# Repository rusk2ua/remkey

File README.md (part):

# remkey — remote paddle CW for the IC-7610 (or any rig with a KEY jack)

> **Status:** the software is complete and tested in CI (simulation, end-to-end network tests, and firmware builds for every Nano image), and it now runs end to end on the author's station (Oct 2026): a Mac paddle over Tailscale keys the IC-7610 and its tower-mounted 10 GHz transverter, with graceful PTT release and every safety stop checked. The tower telemetry (remtlm) has not yet run on real hardware. Sections 7 and 9 have the first-power-up checklists. Reports from real stations are very welcome.

Send CW with your own paddle from anywhere, with an instant local sidetone, and have the shack re-key it with perfect timing. Remote PTT (the TRANSMIT button) included.

remkey is built for a station where:

- A Windows PC in the shack already runs N1MM+, rig control and rotator control, and you reach it with AnyDesk.
- The 7610 drives a tower-mounted 10 GHz transverter through its SEND line, so PTT is manual and keying is CW.
- You travel with a Mac and want to use a real paddle.

It is two Arduino Nanos running the same sketch, plus a small Python bridge. Optional extra Nanos (**remtlm**, section 9) bring tower-top PA power, temperatures, reference lock and Kuhne transverter status, plus the tower supply's voltage and current from a box at the tower base, into the radio room over a LoRa link.

**Quick start:** wire and flash the Nanos (sections 1–3), run the station service on the shack PC (section 4), pick a network path (section 5), and run the client on your Mac (section 6). Do the bench test (section 7) before connecting anything to the tower. For a step-by-step checklist from ordering parts to a hardened station, see [docs/build-plan.md](docs/build-plan.md).

## How remkey works

**In one paragraph:** remkey lets you send CW with your own paddle, from anywhere with an internet connection, through the radio in your shack. A keyer at your end turns your paddle into characters, the characters cross the internet, and a second keyer in the shack sends them to the radio with perfect timing. You hear your own sidetone instantly, and the radio's real sidetone comes back in the receive audio a moment later.

**1. At the travel end, you hear yourself instantly.** The paddle and a PTT switch plug into an Arduino Nano that is an ordinary iambic keyer with its own sidetone, so there is no delay at all in what you hear. As you send, it decodes each character and passes it over USB to the remkey client on the Mac. The client also lets you type CW from the keyboard, has hotkeys for PTT, speed and a tune carrier, and shows tower readings.

**2. Only characters cross the network.** Sending raw key-down and key-up events over the internet doesn't work: network jitter stretches and chops the elements. remkey sends whole characters instead, along with PTT commands and a heartbeat every second, over an authenticated TCP connection (normally inside a Tailscale tunnel). Jitter can delay a character, but it can never distort one.

**3. The shack re-times them perfectly.** The station service on the shack PC checks the client's login and watches the heartbeat. It hands each character to a second Nano, which keys the IC-7610's KEY jack and SEND (PTT) line through optocouplers with exact timing. The SEND line in turn keys the 10 GHz transverter and PA on the tower. The radio runs about one character behind you, which is under a second at normal speeds.

**Feedback.** When the station has actually turned PTT on, the client's PTT LED lights. The receive audio, including the radio's own sidetone, comes back by AnyDesk, so you can confirm what really went out.

**Safety.** If the connection closes, the heartbeat stops for 3 s, or the shack PC or its USB link hangs (the station Nano has its own 3 s watchdog), PTT drops and any queued CW is thrown away at once. Characters sent while the link is down are dropped, not saved, so stale CW never goes out minutes later. N1MM+, rig control and rotator control keep running on the shack PC as before; remkey only adds the keying path.

The same picture as plain text:

```
  TRAVEL END (Mac)                                         SHACK (Windows PC)
 ┌───────────────────────┐                               ┌─────────────────────────────┐
 │ paddle ─┐             │                               │                             │
 │ PTT btn ┼─► CLIENT    │ USB  remkey.client   TCP/JSON │ remkey.station   USB        │
 │ speaker◄┘   Nano      ├────► (Python)  ─────────────────► (Python)  ──────► STATION │
 │  (local sidetone,     │      keyboard CW,  internet   │  auth, heartbeat,  Nano     │
 │   decodes paddle      │      hotkeys       (port-fwd  │  safety-off on     │        │
 │   to characters)      │                   or Tailscale│  link loss         │        │
 └───────────────────────┘                     tunnel)   │       opto ─► KEY jack      │
                                                         │       opto ─► PTT/SEND      │
                                                         │  N1MM+ / SO2R+ untouched    │
                                                         └─────────────────────────────┘
```

## Why it works this way

Sending raw key-down/key-up events across the internet doesn't work: network jitter stretches and chops your dits and dahs. remkey splits the job instead:

1. **At your end,** the client Nano is a normal iambic keyer with its own sidetone. You hear yourself with zero latency. It decodes each character you send and reports it over USB, for example `K:C`.
2. **Characters** cross the network, not element timing.
3. **At the shack,** the station Nano re-sends each character with exact timing on an optocoupler across the 7610's KEY line.

The radio transmits each character roughly one character-time after you send it. That's under a second at 15–20 WPM, which doesn't matter on 10 GHz. You still hear the radio's real sidetone in the remote audio stream (delayed), so you can confirm what actually went out.

Anything the decoder doesn't recognize, such as SK or a fumbled character, is passed through as a raw element pattern like `{...-.-}`. The station sends it element-for-element, so nothing is lost or "corrected."

**Long dash strings (antenna peaking).** Hold the dah paddle and the far end hears zeros: once a 6th dah follows five, the client sends those five as `0` and keeps going, so the station starts sending about one group (~1.3 s at 18 WPM) after you start, rather than after you stop. When you let go, the leftover dashes go out as an ordinary character (T, M, O).

## Contents

```
firmware/remkey/remkey.ino     Nano sketch (both roles)
firmware/remkey/config.h       role, pins, defaults
firmware/platformio.ini        optional PlatformIO/VS Code build
firmware/remtlm/               tower telemetry over LoRa (tower, psu + base roles), section 9
host/remkey/station.py         shack service (Windows)
host/remkey/client.py          travel client (macOS; Linux works too)
host/remkey/protocol.py        network protocol, CW text sanitizer
host/remkey/telemetry.py       remtlm packet parsing, calibration, link statistics
host/remkey/tlmview.py         bench viewer for calibrating the PA power sense
host/remkey/powerstats.py      tower supply statistics from the CSV log; suggested alert limits
host/remkey/e220.py            read or program an E220 LoRa module through a USB serial adapter
host/remkey/dashboard.py       telemetry web dashboard served by the station service (section 9)
host/remkey/web/dashboard.html the dashboard page (self-contained: no internet needed)
host/remkey/cloud.py           uploads telemetry snapshots to S3 for the cloud copy (section 9)
cloud/                         CloudFormation template + Mac deploy script for the cloud copy
host/*.example.toml            config templates
host/tests/                    pytest: protocol, end-to-end over localhost, telemetry
tests/firmware_sim/            g++ simulation of the sketch (timing, decoder, watchdog)
.github/workflows/ci.yml       CI: Python on Linux/Windows/macOS, simulation, firmware builds
docs/build-plan.md             phased build checklist, parts to tower installation
docs/serial-commands.md        sending CW by hand from the Serial Monitor
CHANGELOG.md                   per-component versions and changes
CONTRIBUTING.md, SECURITY.md   how to run the checks; security model and reporting
```

---

## 1. Hardware

Circuit boards for all three nodes (KiCad, with JLCPCB-ready Gerbers) are in [`hardware/`](hardware/README.md). A bench prototype of the shack and supply-box nodes on ElectroCookie boards is in [`docs/prototype/`](docs/prototype/README.md).

### Parts

| Qty | Part | Notes |
|---|---|---|
| 2 | Arduino Nano (ATmega328P) | Clones are fine. CH340 USB chips need no driver on current macOS or Windows. |
| 2 | PC817 (or 4N25/4N35) optocoupler | Station only: one for KEY, one for PTT |
| 2 | 470 Ω resistor | Opto LED current, about 8 mA with bare PC817s |
| 2 | 220 Ω resistor | Instead of the 470 Ω, with a ready-made 2-channel opto board (its indicator LED drops extra voltage; see Station Nano) |
| 1 | 3.5 mm stereo jack | Client paddle input |
| 1 | Momentary pushbutton/footswitch, or an SPST toggle switch | Client PTT (set `ptt_switch` in `client.toml`) |
| 1 | Piezo sounder or small speaker + 100 µF cap | Client sidetone; or feed a headphone amp |
| 1 | 220 Ω resistor | Sidetone series resistor |
| 1 | 10 kΩ pot (optional) | Client speed knob. Set `USE_SPEED_POT 1`. |
| — | Cables to the 7610 KEY jack and PTT line | Station |

### Client Nano (travel keyer)

| Nano pin | Connects to | Notes |
|---|---|---|
| D2 | Paddle jack **tip** (dit) | Internal pull-up; the paddle contact closes to GND |
| D3 | Paddle jack **ring** (dah) | Internal pull-up; the paddle contact closes to GND |
| GND | Paddle jack **sleeve**, and the GND side of everything below | Common ground |
| D4 | PTT switch, other side to GND | SPST toggle: `ptt_switch = "latching"`. Momentary button or footswitch: `ptt_switch = "momentary"` (in `client.toml`) |
| D9 | 220 Ω → piezo (+); piezo (−) to GND | Sidetone. Or 220 Ω → 100 µF → small amp/headphone input, with 10 kΩ to GND for level |
| D12 | 1 kΩ → LED anode; LED cathode to GND | Optional. Lights when the **station** confirms PTT is on |
| A0 | 10 kΩ pot wiper; pot ends to 5V and GND | Optional speed knob. Set `USE_SPEED_POT 1` in `config.h` |
| 5V | Top of the speed pot | Only needed with the pot |
| D13 | On-board LED (no wiring) | Flashes with every element you send |
| USB | Mac | Power and serial |

Swap paddles in `config.h` (`SWAP_PADDLES`) instead of rewiring.

**LEDs (both roles):** the on-board LED (D13) flashes with the CW being sent: paddle elements on the client, re-keyed text on the station. `LED_ACTIVE_LOW` in `config.h` sets its polarity. It's 1 by default, for clones whose LED lights on LOW; set it to 0 for a genuine Nano. PTT state goes to an optional external LED on D12 (D12 ── 1 kΩ ── LED ── GND).

### Station Nano (shack)

```
            ┌──────────── PC817 #1 ─────────────┐
D10 ─ 470Ω ─┤1 anode               collector  4 ├── KEY line (tip) ──► 7610 KEY
GND ────────┤2 cathode             emitter    3 ├── KEY ground (sleeve)
            └───────────────────────────────────┘
            ┌──────────── PC817 #2 ─────────────┐
D11 ─ 470Ω ─┤1 anode               collector  4 ├── PTT/SEND-in line ──► 7610
GND ────────┤2 cathode             emitter    3 ├── chassis ground
            └───────────────────────────────────┘
```

The block diagram above shows bare PC817 chips with 470 Ω drive. The schematic below uses a modified ready-made 2-channel PC817 board instead, driven through 220 Ω (details of the modification follow).

| Nano pin | Through | Board terminal | Board output | Goes to |
|---|---|---|---|---|
| D10 (KEY) | 220 Ω | IN1 | V1 | 7610 KEY jack tip, Y-cabled with the SO2R+ keying output |
| D11 (PTT) | 220 Ω | IN2 | V2 | SO2R Box rear RCA **PTT** jack, center pin |
| GND | — | G (input side) | G (output side) | KEY sleeve and RCA shell (radio-side ground; *not* tied to the Nano GND) |

The optocouplers keep the Nano and PC USB ground galvanically separate from the radio, which matters on a station with a tower.

**Ready-made 2-channel PC817 boards** (sold as "817 Module 2 Channel Isolation") need two changes before they'll work here. Each channel has a 3 kΩ chip resistor (marked `302`) on the input side **and another in series with the output**:

- **Input 302:** in series with your own resistor it starves the LED (about 0.4 mA). Remove it and bridge the pads, then drive the LED from the Nano through 220 Ω: about 3 V across the board's input, LED clearly lit.
- **Output 302:** it forms a divider with the radio-side pull-up, so the "closed" output only gets down to about 1.6 V into a footswitch input with a pull-up of a few kΩ. KEY may still work while PTT doesn't. Remove it and bridge the pads; the closed output then reads about 0.1–0.2 V.
- The yellow jumper on each channel ties the output's emitter side to the board ground. Leave it off to keep the radio side fully isolated from the Nano.

With the 302s gone nothing on the output limits current, which is fine for key and PTT inputs (a few mA through the radio's own pull-up). Don't use the outputs to switch anything powered.

**KEY connection.** Both the SO2R+ and the remkey optocoupler are open-collector closures to ground, so they can safely share one line. Either:

- Y-cable the opto output in parallel with the SO2R+ keying output on the rear KEY jack (simplest; N1MM+ keeps working), or
- use the 7610's other key jack, configured for a straight key / external keyer.

Collector goes to the key line (tip), emitter to ground (sleeve). If keying does nothing, reverse it.

**PTT connection.** The opto has to put the *radio* into transmit, just like your TRANSMIT button. Your DC injector stays on the radio's SEND output and keeps working unchanged. Use an input that forces TX:

- **ACC socket SEND line:** on many Icom rigs this pin is bidirectional (it goes low on TX, and grounding it forces TX). Check the IC-7610 full manual's ACC pinout before wiring.
- **Front MIC connector PTT pin:** always a TX input. Check the manual for the pin number.

Do **not** wire the opto to the SEND output that drives your DC injector. That would key the transverter without the radio being in transmit.

**With a YCCC SO2R Box (plus):** the simplest PTT input is the box's rear RCA **PTT** footswitch jack. It keys the transmit-focus radio's PTT through the box's radio cable, so your SEND-driven sequencing works unchanged. (The DB25 is the box's auxiliary connector and has no PTT or key pins.) This is what the author uses, with the KEY opto in parallel with the box's keying output; N1MM+ and a local paddle through the box keep working.

---

## 2. Radio settings (IC-7610)

- **Break-in: OFF while operating remotely.** Then nothing goes up the IF cable unless PTT is on, which matches how you already operate (TRANSMIT first, then key). It also means stray keying with PTT off produces sidetone only.
- The jack the opto keys must be set for a **straight key / external keyer**, not paddles. The station Nano is the keyer.
- Keep the 7610's USB audio codec streaming to the shack PC so you can hear receive audio (and the radio's sidetone) through AnyDesk. See section 6.

---

## 3. Firmware

Build with the Arduino IDE (board **Arduino Nano**; processor "ATmega328P", or "Old Bootloader" for most clones) or with PlatformIO in VS Code.

**Arduino IDE.** Open `firmware/remkey/remkey.ino`. In `config.h`, set

```c
#define REMKEY_ROLE ROLE_CLIENT     // for the travel Nano
#define REMKEY_ROLE ROLE_STATION    // for the shack Nano
```

and upload each.

**PlatformIO:**

```
cd firmware
pio run -e client  -t upload --upload-port /dev/cu.usbserial-110
pio run -e station -t upload --upload-port COM7
```

**Check it.** Open a serial monitor at 115200 baud with line ending set to newline. You should see `V:remkey 0.4.1 client` (or `station`; the number is the firmware version). Type `?` to get a status line. On the client, send a few characters with the paddle and you'll see `K:` lines. On the station, `T:CQ` keys the opto and `P:1` / `P:0` drive PTT.

Station watchdog: with PTT on or text queued, if the Nano hears nothing from the PC for 3 s it drops PTT, flushes text and prints `!:WDOG`. The service sends a heartbeat every second, so this only fires if the service or PC hangs.

The serial command set is documented at the top of `remkey.ino`. For keying a Nano by hand from the Serial Monitor, see [docs/serial-commands.md](docs/serial-commands.md).

---

## 4. Shack PC: station service (Windows)

1. Install Python 3.11+ from python.org (tick "Add to PATH").
2. Install remkey:
   ```
   cd remkey\host
   .\Install-remkey.bat
   ```
   It installs into the same Python that `Start-remkey.bat` (step 6) runs: `host\.venv` if you've made one, otherwise `py`. Use it for every later update too (`git pull`, then `.\Install-remkey.bat`). Installing with a bare `py -m pip ...` while a `.venv` exists puts packages where the station never looks: the code itself still updates, because the install is editable, but new dependencies (like boto3 for the cloud copy) go missing.
3. Configure:
   ```
   py -m remkey.genkey                  (copy the output)
   copy station.example.toml station.toml
   ```
   Edit `station.toml`: paste the secret and set `keyer_port` to the station Nano's COM port (Device Manager → Ports; *not* the SO2R+ or 7610 port).
4. Test without hardware:
   ```
   py -m remkey.station --config station.toml --dry-run
   ```
5. Run for real:
   ```
   py -m remkey.station --config station.toml
   ```
6. To start it automatically, use `host\Start-remkey.bat`. It runs the service from the `host` folder (using `host\.venv` if you made one, otherwise `py`), titles the window "remkey station", and if the service ever stops it leaves the window open with the exit code. Create a Task Scheduler task:
   - **Name:** remkey station. **Trigger:** At log on (your user).
   - **Action:** Start a program. **Program/script:** the full path to `Start-remkey.bat`. **Start in:** the `host` folder.
   - **Turn off console QuickEdit** for your user, once, in a Command Prompt:
     ```
     reg add HKCU\Console /v QuickEdit /t REG_DWORD /d 0 /f
     ```
     With QuickEdit on, a click in the window while it's opening at logon can put it into "Select" mode, which freezes the service until a key is pressed. remkey also turns QuickEdit off itself, but only once Python has started. The registry setting closes that gap.

   To check it, reboot, and before touching the window, connect a client and key PTT. Log lines should appear without pressing anything.

The service logs to the console and `remkey-station.log`. It accepts one client at a time.

---

## 5. Getting from the road to the shack

The client makes one outbound TCP connection. Pick one option; all work with the same software.

### Recommended: Tailscale

Encrypted, nothing exposed on the router, and it works with a VPN such as NordVPN running on the shack PC. Set `listen_host = "127.0.0.1"`, publish the port to your tailnet with `tailscale serve --bg --tcp 7373 tcp://127.0.0.1:7373`, and point `station_host` at the shack PC's Tailscale address. Full setup, including NordVPN coexistence: [docs/remote-access-tailscale-nordvpn.md](docs/remote-access-tailscale-nordvpn.md).

### Option A: router port-forward (free)

- On the Spectrum router, forward **TCP 7373** to the shack PC's LAN IP. Give the PC a DHCP reservation first.
- Windows Defender Firewall: allow inbound TCP 7373 for `python.exe`. Windows usually prompts on first run.
- In `station.toml`, set `listen_host = "0.0.0.0"`.
- In `client.toml`, set `station_host` to your public IP. Check it from the shack PC over AnyDesk if it ever changes.

**Security model:** a challenge-response HMAC with your secret (a fresh nonce every connection, so it can't be replayed), one client at a time, and a CW text whitelist. Traffic isn't encrypted. CW text isn't secret, and the risky operation is PTT, which needs the secret. Use a long generated secret.

### Option B: AnyDesk TCP tunnel (nothing exposed on the router)

This requires an AnyDesk plan that includes TCP tunneling.

1. In `station.toml`, set `listen_host = "127.0.0.1"`.
2. In AnyDesk on the Mac, open the shack PC's entry and choose **TCP tunnel → forward**: local port 7373 → `127.0.0.1:7373` on the remote side.
3. In `client.toml`, set `station_host = "127.0.0.1"`. The tunnel exists only while the AnyDesk session is open.

---

## 6. Mac: client

1. Install Python 3.11+ (`brew install python`), then:
   ```
   cd remkey/host
   python3 -m pip install -e .
   cp client.example.toml client.toml
   ```
   Paste the same secret, and set `station_host`, `station_port` and `keyer_port` (`ls /dev/cu.usbserial-* /dev/cu.usbmodem*`).
2. Run it in a terminal window:
   ```
   python3 -m remkey.client --config client.toml
   ```
   Without the travel Nano you still get keyboard CW: add `--dry-run`.

### Hotkeys

| Key | Action |
|---|---|
| PTT button on the keyer, or **Ctrl-T** | Toggle station PTT (the D12 PTT LED lights when the station confirms). Turning PTT off is a graceful release (see below). Pressing it again during the release keeps PTT on. |
| PTT toggle switch (`ptt_switch = "latching"`) | ON turns station PTT on, OFF is the graceful release. After a safety stop with the switch still ON, turn it off and on again to transmit; a switch left ON when the client starts doesn't key. Ctrl-T still toggles. |
| **Esc** | Abort queued text and any tune carrier. During a release, also drops PTT immediately. |
| **Ctrl-U** | Tune carrier (`tune_ms`, capped by the station). Needs PTT on. |
| **Ctrl-F / Ctrl-S** | Speed +1 / −1 WPM, both ends |
| **Ctrl-G** | Status: link, PTT, WPM, round-trip time (plus tower telemetry if fitted) |
| **Ctrl-P** | Tower: PA power, transverter power, temperatures, 10 MHz reference lock |
| **Ctrl-K** | Tower: Kuhne MKU 10 G5 status (`s`) and firmware version (`v`) |
| **Ctrl-V** | Tower: supply voltage and current, measured cable resistance and drop |
| **Ctrl-Q / Ctrl-C** | Quit. With PTT on, it first lets the station finish sending and release PTT (up to 15 s). Press again to quit at once. |
| Typing | Sent as CW. Enter sends a space. `<SK>`, `<AR>`, `<BT>`, `<KN>` send prosigns. |

### A typical 10 GHz QSO

1. In AnyDesk, set the frequency and point the dish with GH Everyware as usual.
2. Press the PTT button. Wait for the PTT LED (station confirmed), then wait for the tower sequencer as you would locally.
3. Send with the paddle. Your local sidetone paces you; the remote audio lets you confirm.
4. Press the PTT button again when you've finished sending. You don't need to wait for the station to catch up: it keys out everything still queued, holds PTT for 2 s more, then drops it. The client shows `STATION PTT releasing` until then, and the PTT LED stays lit.

### PTT release

The station runs about one character behind you, so pressing PTT off right after your last character would otherwise cut it short. Instead, PTT-off is a graceful release:

- The station Nano keys out everything already queued, then holds PTT for `ptt_hang_ms` (2000 ms by default, set in `station.toml`).
- Any CW that arrives during the hold (a character still in flight from the paddle, or you deciding to keep sending) is keyed and restarts the hold. **PTT never drops while CW is still being sent.** There is no upper limit; the hold ends only when nothing has been sent for the hang time.
- Pressing PTT again during the hold keeps PTT on. **Esc** during the hold drops PTT at once.
- The client Nano reports a character you've just finished before the PTT button press, so it reaches the station ahead of the release.
- The safety stops below are never delayed by the hold.

### Audio

The receive audio path is independent of remkey. AnyDesk's own audio transmission carries it one way (radio → shack PC → Mac); this setup is verified on the IC-7610, on Windows 10 and on Windows 11 with AnyDesk 9. Open the classic Sound panel with **Win+R → `mmsys.cpl`** (Windows 11: Settings → System → Sound → More sound settings).

1. **Sound → Recording:** the 7610's input (e.g. *Microphone – 3- USB Audio CODEC*, or the name you gave it) → Properties → **Listen** → tick **Listen to this device**, playback through the default output chosen by name. **Leave it ticked permanently:** it isn't a test feature, it's the only thing that puts the radio's audio where AnyDesk can capture it. It's stored per device, so it doesn't survive a move to a new PC or a new USB port.
2. **Sound → Playback:** the default (green check) is the PC's normal output, e.g. an HDMI monitor. It doesn't need speakers; it just has to show *Ready* / *Default Device*. **Never** make *Speakers – USB Audio CODEC* the default: that's the radio's transmit input.
3. **AnyDesk on the shack PC → Settings → Audio:** **Audio Transmission = "Audio output of this device"**, not the radio's codec. (Pointing it at the codec sends the silent transmit side, so the Mac hears nothing.)
4. **AnyDesk → Settings → Permissions** (AnyDesk 9: **Settings → Access**): "Hear my device's sound" ticked in both the **Unattended Access** and **Default** profiles.
5. **Restart AnyDesk on the shack PC and reconnect** after any audio change; a running session doesn't pick it up.

Quick check: play a YouTube video on the shack PC. If you hear it on the Mac but not the radio, the Listen box (step 1) is unticked or points at a different output. Don't go by the Playback tab's level meter: on AMD HDMI/DP audio (GMKtec G10) it stays flat even when audio is flowing; the Intel NUC's meter moved. Use the Recording tab meter to see the radio reaching the PC, and your ears on the Mac for the rest. If an HDMI monitor sleeps, Windows may drop its audio device, so set the display to never turn off. Before relying on it, confirm the radio's CW sidetone is present in the stream: key the rig locally with BK-IN off and listen.

### Safety layers

Every one of these drops PTT and flushes queued text **immediately**, with no release hold:

| Event | Where |
|---|---|
| TCP connection closes or errors | station service |
| No heartbeat from the client for 3 s (dead hotel Wi-Fi, laptop sleeps) | station service |
| Station service or PC hangs, USB unplugged | station Nano watchdog (3 s) |
| Tune carrier | capped by the service (`max_tune_ms`) and the firmware (30 s hard cap) |

Quitting the client is not on this list: it requests a normal release and waits for it (up to 15 s, or press Ctrl-Q again).

Paddle characters sent while the link is down are **dropped**, not buffered, so stale CW never goes out minutes later.

---

## 7. Bench test before connecting to the tower

1. Station Nano on the PC, opto outputs to a multimeter (continuity) or LEDs, not the radio yet.
2. Run the service, connect the client on the same LAN (`station_host` = the PC's LAN IP), and check:
   - PTT button → PTT opto closes, D12 PTT LED on at both ends.
   - Paddle → KEY opto follows about one character behind; local sidetone is immediate.
   - Kill the client's Wi-Fi with PTT on → PTT opens within 3 s.
   - Stop the service with PTT on → the Nano opens PTT within 3 s (`!:WDOG`).
   - Unplug the station Nano's USB with PTT on → PTT opens at once (the Nano loses power). Plug it back in: the service reconnects and re-arms it by itself.
   - Unplug the client Nano's USB with PTT on → the client releases PTT gracefully (queued CW still goes out, then the hang). Plug it back in: the paddle works again without restarting the client.
3. Connect to the 7610 into a dummy load at the IF with the transverter disabled. Check KEY polarity and PTT.
4. Test from your phone's hotspot over the port-forward or tunnel.

---

## 8. Development

```
cd host && python3 -m pip install -e ".[test]" ruff && ruff check . && python3 -m pytest -q
tests/firmware_sim/run.sh       # needs g++; runs the sketch against a mock Arduino
```

GitHub Actions runs all of this on every push and pull request, plus an `arduino-cli` build of every firmware image (remkey client and station; remtlm tower, tower with its own INA226, base and psu). The resulting `.hex` files are attached to each CI run as artifacts. See CONTRIBUTING.md.

The firmware simulation checks:

- PARIS at 20 WPM takes exactly 46 units with 22 units of key-down.
- Raw patterns and word spacing.
- Iambic A/B squeeze behavior.
- Paddle decode of `CQ TEST K2UA`, and unknown patterns.
- Tune timing and the 30 s cap.
- The watchdog, with and without heartbeats.
- PTT button debounce.
- That the client paddle never drives the KEY output.
- remtlm (mocked E220, OneWire and INA226): the psu node slots its `$RS` ~60 ms after each tower `$RT`, falls back to its own 2 s timer when the tower is silent, ignores corrupt packets, reports a missing INA226 and a reversed shunt; the tower sends `$RP` only with `PWR_ENABLE 1`; the base forwards `$RS` and counts bad packets.

Every firmware image builds with no warnings in the project's own files (`arduino-cli`, board Arduino Nano, `--warnings all`):

| Image | Flash | Static RAM |
|---|---|---|
| remkey client / station | 7.9 KB of 30 KB | 541 B of 2 KB |
| remtlm tower with its own INA226 (`PWR_ENABLE 1`; 0.3.0 figures) | 18.8 KB | 1056 B |
| remtlm psu | 17.5 KB | 832 B |
| remtlm base | 7.8 KB | 458 B |

Library versions used in CI: EByte LoRa E220 library 1.0.8, OneWire 2.3.8, DallasTemperature 4.0.6.

## 9. Tower telemetry (remtlm)

Three more Nanos bring tower readings into the radio room over one LoRa channel. Two of them transmit, from two boxes on the tower, and one receives in the shack.

### How remtlm works

**In one paragraph:** remtlm tells you what's happening on the tower while you operate. Two small boxes on the tower measure the things the radio can't see, such as PA output, reference lock, temperatures, supply voltage and dish elevation, and send them by LoRa radio to a receiver in the shack. The station service that already runs remkey turns the readings into hotkey readouts, alerts, a live web dashboard and an optional cloud copy you can check from anywhere.

**1. The tower-top box reports what the rig can't see.** A Nano in the box on the back of the dish watches the PA's power-sense output, the transverter's own power monitor, its 10 MHz reference lock and its key line to the sequencer, sampling every 5 ms so that even a single CW dit is caught. It also reads two temperature probes, the transverter's serial status (read-only), the dish elevation from an ADXL355 on the dish frame, and the box's air temperature, humidity and pressure. It sends a short report every 2 seconds, every half second while the PA is transmitting, and an elevation reading 5 times a second while the dish moves.

**2. The supply box reports on its own.** A second Nano, in the supply box at the tower base, measures the voltage and current going up the tower cable and the box temperature. It is separate so it can be built first and keeps reporting even if the top box is down. Both boxes share one radio channel: the supply box listens for each tower report and sends its own in the gap right after it, so the two never collide.

**3. One program shows it everywhere.** In the radio room, a third Nano with its own LoRa radio checks every packet and adds the signal strength, then passes it over USB to the station service. The service applies the calibrations, raises alerts (reference unlock, over-temperature, low or high supply, the transverter keyed but no PA output, a stuck key line, humidity or condensation in the box, a box gone silent), logs everything to a CSV file, and shows it on the Mac client's hotkeys, a live web dashboard and an optional read-only cloud page.

**Why radio, and why it's safe.** The LoRa link means there is no wire between the tower and the house, so it adds no lightning path. Telemetry uses its own USB port, separate from the remkey station Nano, so a telemetry fault can't affect keying. Nothing in remtlm can key the radio or change the transverter's settings: the tower only ever asks the transverter for its status.

### What each box measures

The **tower-top box** (TOWER image) is set up for a **Kuhne MKU 10 G5** transverter and an external PA:

- **PA power sense** (0–5 V), peak and average, sampled every 5 ms so CW dits aren't missed
- **MKU MON** output (CON1 pin 9), the transverter's own power monitor
- **10 MHz reference lock** from the MKU's LD output (CON1 pin 16); any unlock during a reporting interval is reported
- **The key line to the sequencer** (MKU CON1 pin 8, PTT out, active low; tower firmware 0.6.0+): whether it was keyed during each interval, and its voltage. Changes are reported right away. It tells you which side failed when the MKU transmits but the PA doesn't, and it catches a key line stuck low
- **Two DS18B20 probes**: PA heatsink and MKU case
- **The MKU's serial status**: the `v` (firmware) reply once after boot, then the `s` (status) reply every minute, relayed verbatim
- **Dish elevation** (tower firmware 0.7.0+): one ADXL355 on the frame that carries both dishes (10 and 24 GHz, one actuator). The dashboard shows it on an analog-style dial, updated 5 times a second while the dish moves
- **Box air** (0.7.0+): a BME280 in the box for temperature, humidity, pressure and dew point, with a condensation alert

The **supply box at the tower base** (PSU image) is separate, so it can go in before the top box and keeps reporting if the top box is down:

- **Supply voltage and current** going up the tower, from an INA226 and a shunt at the supply output: min, average and peak for every interval
- **One DS18B20** for the box temperature
- Its own sequence number and uptime, so the station tracks its link loss and resets separately

The top box can optionally get its own INA226 as well (`PWR_ENABLE 1`). With both, the station shows the **measured cable drop**, works out the **cable's actual resistance**, and checks the voltage the MKU actually sees (see "Supply voltage, current and cable drop" below).

```
 TOWER TOP                                                  RADIO ROOM
┌──────────────────────────────────────────┐            ┌──────────────────────────────┐
│ PA sense ─────────► A0 ┐                  │  927.125   │ E220 ─► BASE Nano ─USB─► PC   │
│ MKU pin 9 MON ────► A1 │                  │    MHz     │  validates packets   station  │
│ MKU pin 16 LD ────► A2 ├─ TOWER ─► E220 ~~~~~~~~~~~~~~►│  from both boxes     service  │
│ MKU pin 8 PTT out ► A3 │                  │            │                              │
│ DS18B20 ×2 ───────► D5 │   Nano     $RT  │    LoRa    │  ─► client: Ctrl-P, Ctrl-K,   │
│ MKU pins 11/12 ◄──► D11/D12 (via shifter)│     ▲      │     Ctrl-V, alerts, TX summary│
│ ADXL355, BME280 (+opt. INA226) ─► A4/A5  │     ║      │                              │
└───────────────▲──────────────────────────┘     ║      └──────────────────────────────┘
                ║ tower cable (+/−)              ║
 TOWER BASE     ║                                ║
┌───────────────╨──────────────────────────┐     ║
│ 14 V supply ═► shunt ═► tower cable       │     ║
│ INA226 on the shunt ─► A4/A5 ┐            │     ║
│ DS18B20 (box temp) ──► D5    ├─ PSU ─► E220 ~~~╝  $RS, just after each $RT it hears
│                              │  Nano      │
└──────────────────────────────────────────┘
```

There is no conductor between the tower and the house, so the link adds no lightning path. Everything ends up in the same station service and Mac client as remkey.

**The transverter link is read-only.** The tower only ever sends `s` and `v`, which read status, never the configuration commands (`IR`/`IT`/`RR`/`RT`/`D1`–`D4`). A garbled byte can't retune the IF or change the sequencer.

### Which Nano is which

With remtlm, the station has up to five Nanos. Each is a separate board on its own USB port or in its own box; the remtlm base does **not** replace the remkey station Nano.

| Nano | Where | Firmware | Connects to |
|---|---|---|---|
| remkey station | Shack PC (USB) | remkey, station role | `keyer_port` in `station.toml`, and the 7610 keying lines |
| remtlm base | Shack PC (USB) | remtlm 0.5.0, base | `tlm_port` in `station.toml`, plus its own E220 |
| remtlm psu | Supply box at the tower base | remtlm 0.4.0, psu | Its own E220, INA226, DS18B20 |
| remtlm tower | Tower-top box | remtlm, tower | Its own E220, PA and MKU sense lines, probes |
| remkey client | Travel end (Mac, USB) | remkey, client role | Paddle and PTT switch; the Mac client by USB |

The station service opens both shack ports. The keying path and the telemetry path share no hardware, so a telemetry fault can't affect keying: unplugging the remtlm base only raises a "lost" alert.

### Frequency and legality

- The link runs on **927.125 MHz** (E220-900T22D channel 77, set by `LORA_CHANNEL` in `firmware/remtlm/config.h`). That's the top of the US 902–928 MHz band and about 24 MHz clear of 902–903 weak-signal work.
- Treat the link as part of your **amateur station (Part 97)**. 927 MHz is in the 33 cm band, the packets are plain ASCII with no encryption, every packet carries your callsign, and §97.221(b) allows automatic control of data emissions on 6 m and shorter. It is *not* a Part 15 device in this configuration: a single-channel module at 17 dBm doesn't fit the unlicensed rules.
- Airtime: roughly 60–70 ms per packet at the 9.6 kbps air rate. The top box sends a `$RT` every 2 s while idle and every 0.5 s while the PA shows output (plus a `$RP` before each one if it has its own INA226). With the 0.7.0 sensors it adds a `$RA` (elevation, ~50 ms) before each `$RT`, a `$RB` (box air) every 10 s and a `$RC` (the BME280's calibration constants) every 5 minutes, all just ahead of a `$RT`.
- **Live elevation.** While the dish moves, the tower sends a `$RA` every 200 ms, until it has been still for 3 s; that uses about a quarter of the channel while it lasts, and nothing when the dish is parked. Live packets skip the 450 ms after each `$RT`, which is the supply box's slot, so the supply box keeps reporting while the dish moves. No MKU status poll starts while the dish moves.
- **Two transmitters, one channel.** The base E220 can only listen on one channel, so both boxes use channel 77. To keep them from colliding, the supply box listens too: it sends its `$RS` about 60 ms after the end of each tower `$RT` it hears, in the gap before the tower's next packet, which is at least 0.5 s away. If it hears no tower packet for 3.5 s (top box down, or not built yet), it sends every 2 s on its own timer. It never sends more often than every 0.4 s.
- Transmit power defaults to 17 dBm, which is plenty for 200 ft through block. Raise it with `LORA_TX_POWER` if the link is marginal.

### Parts

| Qty | Part | Notes |
|---|---|---|
| 3 | Ebyte E220-900T22D | All must be the **900** version |
| 3 | 915 MHz antenna (SMA) | A whip is fine; a small yagi at the house end if needed |
| 3 | Arduino Nano | Tower top, supply box, radio room |
| 9+9 | 1 kΩ and 2 kΩ resistors | 5 V → 3.3 V dividers on E220 M0, M1 and RXD, at each Nano |
| 3 | 100 µF electrolytic | Across the E220 VCC/GND pins (TX current peaks) |
| 2 | Mini buck module, fixed 5 V output (5–28 V in) + 0.5 A-hold polyfuse (e.g. RXEF050) | Tower top and supply box: supply → 5 V. Fixed output, nothing to set |
| 1 | AMS1117-3.3 module (or any 3.3 V LDO) | Tower: low-voltage side of the level shifter |
| 1 | 4-channel BSS138 level-shifter module | Tower: Nano ↔ MKU serial (3.3 V) |
| 2 | DS18B20 waterproof probes + one 4.7 kΩ resistor | Tower: both on one bus |
| 2 | 10 kΩ + 22 kΩ resistors, 100 nF caps | Tower: input dividers for A0 and A1 |
| 1 | 100 kΩ resistor | Tower: pull-down on A2 (LD) |
| 1 | 100 kΩ + 47 kΩ + 22 kΩ resistors, 100 nF cap | Tower: key-line network on A3 (MKU CON1 pin 8) |
| — | 2.54 mm female header/jumper wires | Tower: to MKU CON1 |
| 1 | INA226 module (e.g. CJMCU-226) | Supply box: supply monitor. Any I2C address 0x40–0x4F works: the firmware searches for it (0.7.1+) |
| 1 | 20 A / 75 mV panel-meter shunt (3.75 mΩ) | Supply box: in the + feed to the tower cable (see below) |
| 1 | DS18B20 probe + 4.7 kΩ resistor | Supply box: box temperature |
| 1 | Weatherproof box with cable glands | Tower |
| (1+1) | INA226 module + shunt | Optional, tower top (`PWR_ENABLE 1`): measured cable drop |
| 1 | ADXL355 breakout, wired for I2C | Tower (0.7.0+): dish elevation, on its own stiff plate on the dish frame |
| 1 | BME280 breakout (a real BME280: a BMP280 has no humidity) | Tower (0.7.0+): box air |
| 2 | 4-wire leads | Tower: to J2/J3 on RK-302 Rev B, or to the sensor board on a Rev A |

### Wiring: E220 to Nano (same on all three Nanos)

The E220's logic is 3.3 V and not every pin is 5 V tolerant, so the three Nano outputs go through dividers.

```
E220 pin   Nano
M0   ◄──── 2k ──┬── 1k ──── D9        (each divider: Nano ─1k─┬─ E220 pin
M1   ◄──── 2k ──┼── 1k ──── D10                               └─2k─ GND)
RXD  ◄──── 2k ──┼── 1k ──── D8
            GND ┘
TXD  ─────────────────────► D7
AUX  ─────────────────────► D6
VCC  ── 5 V ── 100 µF ── GND
GND  ── GND
```

### Wiring: tower Nano to the MKU 10 G5 and PA

```
13.8 V ── 1 A fuse ── buck (5.0 V) ──► Nano 5V pin (not VIN), E220 VCC, DS18B20s, shifter HV
                     5.0 V ── AMS1117-3.3 ──► shifter LV

PA sense      ── 10k ──┬── A0       MKU CON1 pin 9 (MON) ── 10k ──┬── A1
                       ├─ 22k ─ GND                                ├─ 22k ─ GND
                       └─ 100nF ─ GND                              └─ 100nF ─ GND

MKU CON1 pin 16 (LD) ─────────┬── A2        LD is 3.3 V via 330 Ω when locked; the
                              └─ 100k ─ GND  pull-down holds A2 low otherwise

MKU CON1 pin 8 (PTT out) ──┬── to the sequencer, as before (the tower only listens)
                           ├── 100k ── 5V   an open line reads ~2 V, not "keyed"
                           └── 47k ──┬── A3
                                     ├── 22k ─ GND     keyed (low) reads ~0 V; safe to ~15 V
                                     └── 100nF ─ GND

MKU CON1 pin 11 (TXD) ── shifter LV1 ═ HV1 ── D11
MKU CON1 pin 12 (RXD) ── shifter LV2 ═ HV2 ── D12
MKU CON1 pin 15 (GND) ── GND                (common ground with the Nano)

DS18B20 #1 and #2: red 5V, black GND, both yellow ── D5; one 4.7k from D5 to 5V

Optional (PWR_ENABLE 1 in config.h), a second INA226 at the top-box entry:
INA226 module: VCC ── 5V, GND ── GND, SDA ── A4, SCL ── A5   (A0/A1 address pins to GND)

 from tower cable (+)        20 A / 75 mV shunt            to everything in the box
 +13.8 ══════════► [big bolt]══════════════════[big bolt] ══════► MKU, PA, relays, fuse, buck
                   (sense screw)            (sense screw)
                        │                         │
                       IN+                       IN- ── also VBUS on modules that
                                                        have a separate VBUS pin
```

The same wiring as schematics, in two parts: the signals (PA sense, MKU CON1, level shifter and probes), then the power feed with the optional top-box supply monitor. Without it, the 13.8 V feed goes straight to the fuse and the equipment.

**Notes:**

- **Why analog for LD:** a 5 V Nano needs about 3.0 V to read a digital high, and LD gives only 3.3 V through 330 Ω. That's too close, so A2 compares against 1.65 V instead.
- **LD tracks the external 10 MHz reference:** it's high only while the MKU is locked to an *external* 10 MHz reference. If you run without one, set `LOCK_MONITOR 0` so it doesn't alarm (or, from 0.7.1, add `-DLOCK_MONITOR=0` to the arduino-cli build flags).
- **Probes:**
  - Clamp one DS18B20 under a heatsink screw near the PA device and the other on the MKU housing, both with thermal compound.
  - The MKU is rated for +55 °C case and disables transmit above +65 °C. The default alert for probe 2 is 50 °C.
  - Probe order on the bus is fixed by each probe's serial number, not by wiring. Warm one in your hand while watching `tlmview` to see which is which. Then set `temp_names` in `station.toml`, or swap the probes.
- **ADC reference:** the buck's output is fixed at 5 V, but each module is a little off. Measure the actual rail with a DMM and enter it as `VREF_MV`. The ADC uses that rail as its reference.
- **Command terminator:** if the MKU doesn't answer `s`, it may want a line terminator. Set `XV_CMD_SUFFIX "\r"` in `config.h`.

### Wiring: supply box at the tower base (PSU Nano)

The same Nano and E220 block as the other two, plus the INA226 on a shunt in the supply's + output, and one DS18B20:

```
14 V supply (+) ══╦══► [bolt] 20 A / 75 mV shunt [bolt] ══════► tower cable (+)
                  ║         (sense)        (sense)
                  ║            │              │
                  ║           IN+            IN- (and VBUS, if the module has one)
                  ╚═ 1 A fuse ── buck (5.0 V) ──► Nano 5V pin (not VIN), E220 VCC, INA226 VCC, DS18B20

INA226 module: VCC ── 5V, GND ── GND, SDA ── A4, SCL ── A5   (A0/A1 address pins to GND)
DS18B20: red 5V, black GND, yellow ── D5; 4.7k from D5 to 5V
E220: same as "Wiring: E220 to Nano" above
14 V supply (−) ── tower cable (−) ── box ground (buck, Nano, E220, INA226)
```

- **Take the box's own 5 V from the supply side of the shunt.** Then the INA226 measures only what goes up the tower, not the box's own 30–120 mA.
- **The voltage reported is the supply's output** (load side of the shunt), not the voltage at the top. The cable drop is only measured once the top box has its own INA226; until then, Ctrl-V shows supply voltage and current only.
- **Antenna:** the supply box is closer to the house than the top box, so a whip on the box is plenty. Keep it a few feet from the tower cable.
- **Don't power the Nano from VIN at 14 V.** Its linear regulator would drop 9 V at up to ~120 mA during E220 transmit peaks, more than 1 W in a sealed box. Use a buck module or a 5 V USB supply.

**Supply monitor notes** (the supply box's INA226, and the optional one at the top):

- **Put the shunt ahead of everything it should measure.** In the supply box that is the feed to the tower cable. At the top it is the enclosure entry, ahead of everything including the tower Nano's own buck converter.
- **Heavy wires go on the big bolts; IN+ and IN- go on the small sense screws.** The sense screws give you a Kelvin connection: they measure the shunt element itself, not the resistance of the bolted joints. IN+ goes on the supply side, IN- on the load side.
- **The whole shunt sits at +13.8 V.** Mount it on its insulating base or on standoffs, clear of the metal enclosure, and cover the terminals.
- **Range:** with 3.75 mΩ the INA226 reads up to 21.8 A in 0.67 mA steps. At 4 A the shunt drops 15 mV and dissipates 60 mW; at 8 A, 30 mV and 0.24 W. Panel shunts run cool well below their rating.
- **`SHUNT_UOHM` is 3750 by default.** A different shunt needs only that value changed: millivolt rating ÷ amp rating, in µΩ (75 mV / 20 A = 3750).
- **CJMCU-226 modules have their own 0.1 Ω shunt (R100) on the board.** Remove it. Left in parallel with the panel shunt it makes readings 3.6% low (or set `SHUNT_UOHM 3614`).
- **The bus voltage is read on the load side of the shunt.** At the top that is the voltage your equipment actually sees; in the supply box, it's what goes into the cable. On modules with a separate VBUS pin, tie it to IN-.
- **Negative current means the shunt is wired backwards.** It is reported as-is, not hidden.
- **Trim to your meters:** compare against a DMM at the INA226 and a clamp meter, then set `v_scale` and `i_scale` in `station.toml`. No reflash needed. (One pair of trims covers both INA226s; with good shunts and modules they need little or no trim.)

### Wiring: base Nano (radio room)

Only the E220 block above (its schematic covers all three), plus USB to the shack PC. It receives both boxes; nothing else is needed for the second sender, except that it must run remtlm 0.4.0 or later, because older base firmware rejects `$RS` packets as bad. Put the module and its antenna where it has the best view of the tower, for example a window. A USB extension cable is fine.

### Optional: check each E220 with a USB serial adapter

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
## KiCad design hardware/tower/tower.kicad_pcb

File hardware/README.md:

# remtlm circuit boards

Three two-layer boards for the remtlm telemetry nodes, all through-hole, built by hand, with the modules in sockets:

| Part number | Board | Folder | Size | Goes in | Holds |
|---|---|---|---|---|---|
| RK-301 Rev A | Supply box (PSU) | `psu/` | 102 × 52 mm | Hammond 1590B at the tower base | Nano, INA226 module, mini buck, polyfuse, E220 dividers, one DS18B20 |
| RK-302 Rev B | Tower top | `tower/` | 102 × 52 mm | Hammond 1590B at the tower top | Nano, mini buck, AMS1117-3.3, BSS138 shifter, PA/MKU conditioning, key-line (MKU PTT out) sense, two DS18B20s, I2C headers for the dish elevation sensor (ADXL355) and box air sensor (BME280) |
| RK-303 Rev A | Shack (BASE) | `shack/` | 64 × 40 mm | No enclosure; USB from the shack PC | Nano, E220 dividers |

Part numbers, revisions and the rules for changing them are in [`REVISIONS.md`](REVISIONS.md). Each folder has the KiCad 7 board (`*.kicad_pcb`), a Gerber + drill zip for the fab (`fab/<pn>-rev<rev>-*-gerbers.zip`), a parts list (`*-bom.csv`), top and bottom renders (`img/`) and the DRC report (`*.drc.txt`).

## Checking the fit on paper

Each `fab/` folder has a `*-print-letter.pdf`: the pads, outlines, labels and board edge at full size on US Letter, with a 100 mm scale bar. Print it at 100% (Actual size, not Fit), then measure the bar. It must be exactly 100 mm. Push the modules' pins through the pad dots into a piece of foam or cardboard to check every footprint. (`*-print-1to1.pdf` is KiCad's own A4 plot of the same thing.)

## Ordering (JLCPCB)

Upload the zip from `fab/` as it is. Under "Remove Order Number", choose **Specify a location**: each board has `JLCJLCJLCJLC` printed under the Nano, where JLCPCB will put its number. The defaults are fine: 2 layers, 1.6 mm FR-4, 1 oz copper, HASL. The four buck-module holes are plated slots (1.0 × 2.2 mm). JLCPCB makes those without extra charge, and they show up as slots in the drill file.

## How the boards connect

The nets are the same as the schematics in `docs/img/`:

- `remtlm-psu-box-schematic.svg` (supply box)
- `remtlm-tower-signals-schematic.svg` and the logic-supply part of `remtlm-tower-power-schematic.svg` (tower top; there's no shunt or INA226 at the top)
- `remtlm-e220-schematic.svg` (all three)

The Nano pin numbers match `firmware/remtlm/config.h`. The KiCad files are boards only, not schematic files: each board is described in a short Python script in `gen/`, which places the parts and gives every pad its net. The Python script `gen/route.py` then checks every pad against that list after routing.

### Wires soldered into the board

| Wire | Hole | Pad | Used for |
|---|---|---|---|
| #16 | 1.8 mm | 3.6 mm | Supply in (+ and GND) |
| #18 | 1.4 mm | 2.8 mm | DS18B20 probes (GND, DQ, 5V) |
| #20 | 1.2 mm | 2.4 mm | Shunt Kelvin leads; MKU CON1 pins 11, 12, 16, 9, 15; PA sense and PA ground |

### E220 ribbon

The 1 × 7 header on each board runs M0, M1, RXD, TXD, AUX, VCC, GND, in the module's own pin order. The 5 V → 3.3 V dividers for M0, M1 and RXD are on the main board, so the ribbon carries 3.3 V-level signals. The board has 100 µF + 100 nF at the header. Put another 100 µF across VCC/GND at the E220 end of the ribbon, on the daughterboard.

## Build notes

- **Sockets and headers** (not in the BOMs):
  - Nano: two 1 × 15 female headers on every board.
  - Supply box: a 1 × 8 for the INA226 module.
  - Tower: two 1 × 6 for the shifter, a 1 × 3 for the AMS1117 module, and two 1 × 4 male headers (J2, J3) for the sensor leads.
  - Buck module: four header pins, one in each corner pad.
- **Buck module:** a fixed 5 V output module (5–28 V in), so there's nothing to set; measure its output once for `VREF_MV`. The board marks IN+, IN−, OUT+ and OUT− at the four slots. Check them against the labels printed on the module's underside before soldering. Viewed from above with the inductor on the right, the corners are IN− top-left, OUT− top-right, IN+ bottom-left and OUT+ bottom-right.
- **INA226 module (supply box):**
  - Remove its R100 shunt resistor; the external shunt does the work (or set `SHUNT_UOHM` as the README describes).
  - The board ties VBS to IN−, so bus voltage is measured on the tower side of the shunt.
  - SHUNT+ goes to the supply side of the shunt.
- **Polyfuse:** a radial PTC with 0.5 A hold / 1.0 A trip, rated for at least 30 V (e.g. Littelfuse RXEF050), on 5 mm lead spacing. It protects the board's own logic supply only; the main load current never passes through these boards.
- **Level shifter (tower):** the module sits rotated 180°, LV row toward the transverter wires. LV1 carries MKU TXD (CON1 pin 11) to D11, and LV2 carries MKU RXD (pin 12) from D12. On Rev B, channels 3 and 4 carry the sensors' I2C: LV3/HV3 is SDA (Nano A4), LV4/HV4 is SCL (A5). The module's own 10k pull-ups are the I2C pull-ups on both sides. (On Rev A, channels 3 and 4 are unused.)
- **Sensor headers (tower, Rev B):** J2 (ELEV) for the ADXL355 plate on the dish frame, J3 (AIR) for the BME280 in the box. Both run SDA, SCL, 3V3, GND from the square pad, the same order as the prototype sensor board, so one lead fits either. 3V3 comes from the AMS1117 module; together the two sensors draw about 1 mA.
- **AMS1117-3.3 module (tower):** stands upright in a 1 × 3 socket. The board follows the module's VIN, OUT, GND pin order. OUT is the middle pin.
- **Mounting:** #4-40 hardware (standoff, split washer, pan-head screw) in 3.2 mm unplated holes near the corners: four each on RK-301 and RK-302, three on RK-303. A 7.6 mm circle around each hole is kept free of copper on both sides, so the hardware doesn't touch traces or ground the board to the box.
- **USB:** each Nano sits with its USB end toward the right-hand short wall. Drill one hole there to reflash without opening the box.

## What has and hasn't been checked

Checked:
- KiCad DRC: no clearance errors and no unconnected pads.
- Every pad is on its intended net.
- The Nano pin assignments match `config.h`.
- Paper fit check: the buck, INA226 and Nano matched the full-size prints, and the 100 mm scale bar printed true.
- The board size is inside Hammond's 105 × 53.45 mm maximum for the 1590B, with corner notches for the lid-screw bosses.

Not yet checked:
- Paper fit of the level shifter and the AMS1117 module (from photos only).
- The stack height under the 1590B lid with your standoffs.
- A fabricated board.

The remaining DRC warnings are harmless. Most are notices that the generated boards aren't tied to a KiCad library table. The rest are "starved thermal" notes: a ground pad with fewer than the full set of spokes on one layer, still connected through the other.

## Regenerating

Built with KiCad 7.0 (Ubuntu 24.04 packages) and Freerouting 2.1.0 (Java 21). From `hardware/`:

```
./build.sh
```

Part numbers and revisions come from `boards.json`. This runs `gen/<board>.py` to place parts and assign nets, `gen/route.py` to route with Freerouting, pour GND, run DRC and check the nets, and `gen/fab.py` to write the Gerbers, BOM and renders. Change a script and rerun; routing takes a few seconds per board, and a board is re-routed automatically (up to 5 tries) if Freerouting leaves anything unconnected.

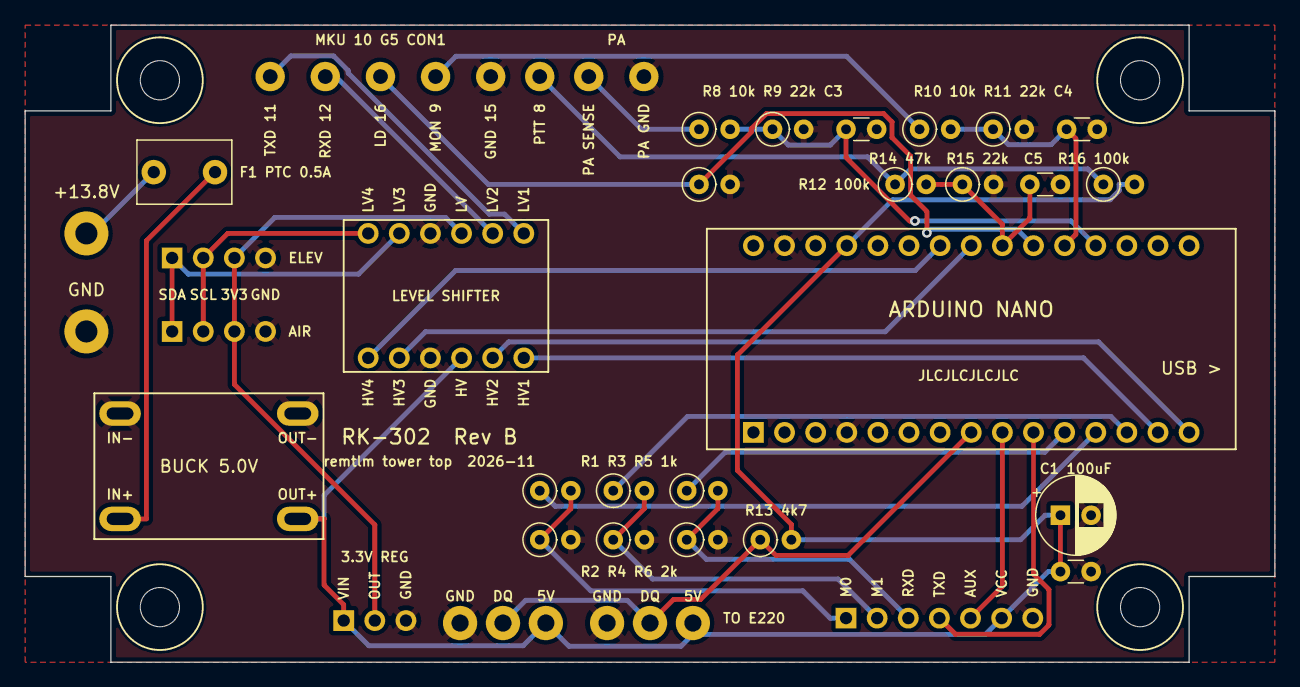
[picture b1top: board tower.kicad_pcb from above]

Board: 2 copper layers, 102.0 x 52.0 mm, 49 parts (0 on the bottom side), 29 nets.

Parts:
C1: 100uF; CP_Radial_D6.3mm_P2.50mm
C2, C3, C4, C5: 100nF; C_Disc_D3.0mm_W1.6mm_P2.50mm
F1: PTC 0.5A hold (e.g. RXEF050); C_Disc_D7.5mm_W5.0mm_P5.00mm
H1, H2, H3, H4: #4-40 mounting hole
J1: E220 ribbon (1x7, 0.1in)
J2: ADXL355 plate lead (1x4, 0.1in)
J3: BME280 lead (1x4, 0.1in)
R1, R3, R5: 1k; R_Axial_DIN0207_L6.3mm_D2.5mm_P2.54mm_Vertical
R2, R4, R6: 2k; R_Axial_DIN0207_L6.3mm_D2.5mm_P2.54mm_Vertical
R8, R10: 10k; R_Axial_DIN0207_L6.3mm_D2.5mm_P2.54mm_Vertical
R9, R11, R15: 22k; R_Axial_DIN0207_L6.3mm_D2.5mm_P2.54mm_Vertical
R12, R16: 100k; R_Axial_DIN0207_L6.3mm_D2.5mm_P2.54mm_Vertical
R13: 4.7k; R_Axial_DIN0207_L6.3mm_D2.5mm_P2.54mm_Vertical
R14: 47k; R_Axial_DIN0207_L6.3mm_D2.5mm_P2.54mm_Vertical
U1: mini buck module, fixed 5 V out (5-28 V in)
U2: AMS1117-3.3 module (1x3 socket)
U3: BSS138 4ch shifter, LV row (1x6 socket)
U4: BSS138 4ch shifter, HV row (1x6 socket)
U5: Arduino Nano (2x15 sockets)
W1, W2: #16 wire
W3, W4, W5, W6, W7, W8, W9, W16: #20 wire
W10, W11, W12, W13, W14, W15: #18 wire

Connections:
+3V3: J2.3, J3.3, U2.2, U3.4
+5V: C1.1, C2.1, J1.6, R13.2, R16.2, U1.4, U2.1, U4.4, U5.12, W12.1, W15.1
A0: C3.1, R8.2, R9.1, U5.4
A1: C4.1, R10.2, R11.1, U5.5
A3: C5.1, R14.2, R15.1, U5.7
AUX: J1.5, U5.22
D8: R5.1, U5.20
D9: R1.1, U5.19
D10: R3.1, U5.18
DQ: R13.1, U5.23, W11.1, W14.1
E_TXD: J1.4, U5.21
GND: C1.2, C2.2, C3.2, C4.2, C5.2, J1.7, J2.4, J3.4, R2.2, R4.2, R6.2, R9.2, R11.2, R12.2, R15.2, U1.2, U1.3, U2.3, U3.3, U4.3, U5.14, U5.27, W2.1, W7.1, W9.1, W10.1, W13.1
LD: R12.1, U5.6, W5.1
M0: J1.1, R1.2, R2.1
M1: J1.2, R3.2, R4.1
MON: R10.1, W6.1
PA_SENSE: R8.1, W8.1
PTT: R14.1, R16.1, W16.1
RXD: J1.3, R5.2, R6.1
SCL: U4.1, U5.9
SCL_3V3: J2.2, J3.2, U3.1
SDA: U4.2, U5.8
SDA_3V3: J2.1, J3.1, U3.2
VFUSED: F1.2, U1.1
VIN: F1.1, W1.1
XV_RX: U4.6, U5.17
XV_RXD: U3.5, W4.1
XV_TX: U4.5, U5.16
XV_TXD: U3.6, W3.1

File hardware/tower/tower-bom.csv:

RK-302 Rev B (2026-11),remtlm tower top,,
Qty,Refs,Value / part,Footprint
1,C1,100uF,CP_Radial_D6.3mm_P2.50mm
4,C2 C3 C4 C5,100nF,C_Disc_D3.0mm_W1.6mm_P2.50mm
1,F1,PTC 0.5A hold (e.g. RXEF050),C_Disc_D7.5mm_W5.0mm_P5.00mm
1,J1,"E220 ribbon (1x7, 0.1in)",custom
1,J2,"ADXL355 plate lead (1x4, 0.1in)",custom
1,J3,"BME280 lead (1x4, 0.1in)",custom
3,R1 R3 R5,1k,R_Axial_DIN0207_L6.3mm_D2.5mm_P2.54mm_Vertical
3,R2 R4 R6,2k,R_Axial_DIN0207_L6.3mm_D2.5mm_P2.54mm_Vertical
2,R8 R10,10k,R_Axial_DIN0207_L6.3mm_D2.5mm_P2.54mm_Vertical
3,R9 R11 R15,22k,R_Axial_DIN0207_L6.3mm_D2.5mm_P2.54mm_Vertical
2,R12 R16,100k,R_Axial_DIN0207_L6.3mm_D2.5mm_P2.54mm_Vertical
1,R13,4.7k,R_Axial_DIN0207_L6.3mm_D2.5mm_P2.54mm_Vertical
1,R14,47k,R_Axial_DIN0207_L6.3mm_D2.5mm_P2.54mm_Vertical
1,U1,"mini buck module, fixed 5 V out (5-28 V in)",custom
1,U2,AMS1117-3.3 module (1x3 socket),custom
1,U3,"BSS138 4ch shifter, LV row (1x6 socket)",custom
1,U4,"BSS138 4ch shifter, HV row (1x6 socket)",custom
1,U5,Arduino Nano (2x15 sockets),custom

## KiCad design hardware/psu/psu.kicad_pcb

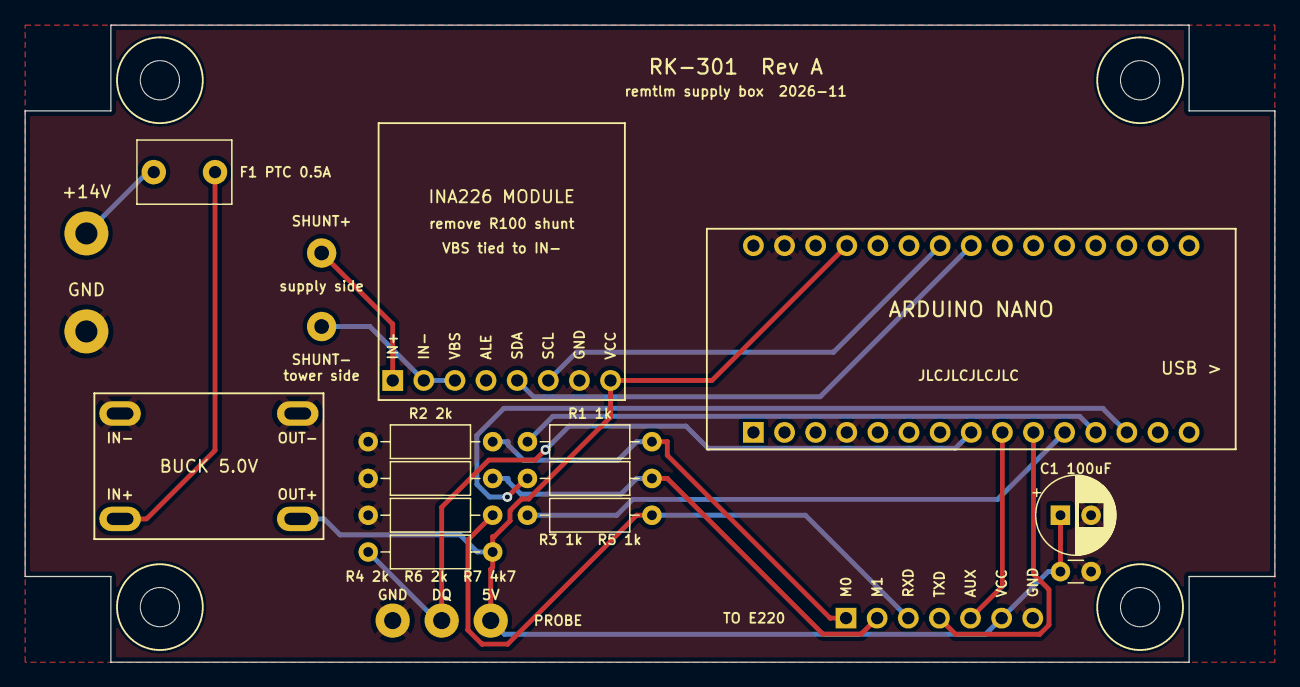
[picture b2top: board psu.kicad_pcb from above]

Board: 2 copper layers, 102.0 x 52.0 mm, 25 parts (0 on the bottom side), 17 nets.

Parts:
C1: 100uF; CP_Radial_D6.3mm_P2.50mm
C2: 100nF; C_Disc_D3.0mm_W1.6mm_P2.50mm
F1: PTC 0.5A hold (e.g. RXEF050); C_Disc_D7.5mm_W5.0mm_P5.00mm
H1, H2, H3, H4: #4-40 mounting hole
J1: E220 ribbon (1x7, 0.1in)
R1, R3, R5: 1k; R_Axial_DIN0207_L6.3mm_D2.5mm_P10.16mm_Horizontal
R2, R4, R6: 2k; R_Axial_DIN0207_L6.3mm_D2.5mm_P10.16mm_Horizontal
R7: 4.7k; R_Axial_DIN0207_L6.3mm_D2.5mm_P10.16mm_Horizontal
U1: mini buck module, fixed 5 V out (5-28 V in)
U2: CJMCU-226 INA226 module (1x8 socket)
U3: Arduino Nano (2x15 sockets)
W1, W2: #16 wire
W3, W4: #20 wire
W5, W6, W7: #18 wire

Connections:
+5V: C1.1, C2.1, J1.6, R7.2, U1.4, U2.8, U3.12, W7.1
AUX: J1.5, U3.22
D8: R5.1, U3.20
D9: R1.1, U3.19
D10: R3.1, U3.18
DQ: R7.1, U3.23, W6.1
E_TXD: J1.4, U3.21
GND: C1.2, C2.2, J1.7, R2.1, R4.1, R6.1, U1.2, U1.3, U2.7, U3.14, U3.27, W2.1, W5.1
M0: J1.1, R1.2, R2.2
M1: J1.2, R3.2, R4.2
RXD: J1.3, R5.2, R6.2
SCL: U2.6, U3.9
SDA: U2.5, U3.8
SH_N: U2.2, U2.3, W4.1
SH_P: U2.1, W3.1
VFUSED: F1.2, U1.1
VIN: F1.1, W1.1

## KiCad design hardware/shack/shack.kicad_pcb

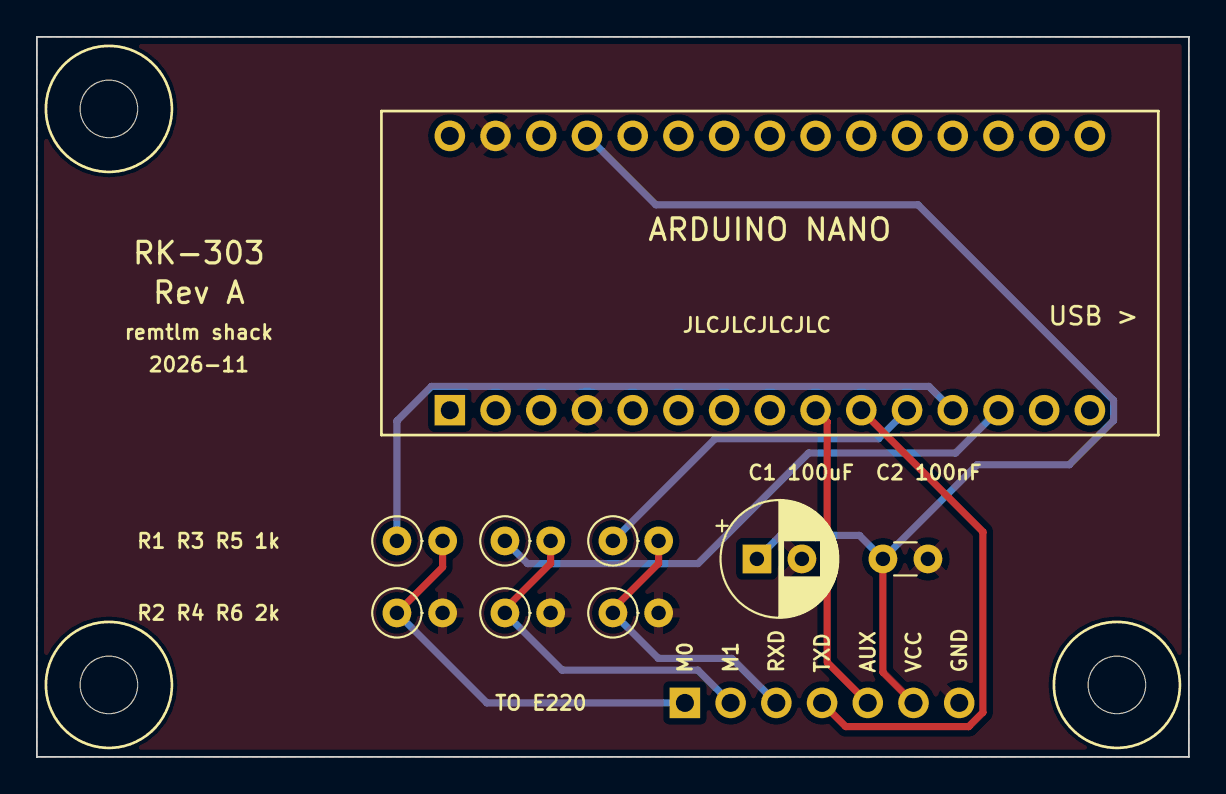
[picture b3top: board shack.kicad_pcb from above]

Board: 2 copper layers, 64.0 x 40.0 mm, 13 parts (0 on the bottom side), 10 nets.

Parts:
C1: 100uF; CP_Radial_D6.3mm_P2.50mm
C2: 100nF; C_Disc_D3.0mm_W1.6mm_P2.50mm
H1, H2, H3: #4-40 mounting hole
J1: E220 ribbon (1x7, 0.1in)
R1, R3, R5: 1k; R_Axial_DIN0207_L6.3mm_D2.5mm_P2.54mm_Vertical
R2, R4, R6: 2k; R_Axial_DIN0207_L6.3mm_D2.5mm_P2.54mm_Vertical
U1: Arduino Nano (2x15 sockets)

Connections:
+5V: C1.1, C2.1, J1.6, U1.12
AUX: J1.5, U1.22
D8: R5.1, U1.20
D9: R1.1, U1.19
D10: R3.1, U1.18
E_TXD: J1.4, U1.21
GND: C1.2, C2.2, J1.7, R2.2, R4.2, R6.2, U1.14, U1.27
M0: J1.1, R1.2, R2.1
M1: J1.2, R3.2, R4.1
RXD: J1.3, R5.2, R6.1

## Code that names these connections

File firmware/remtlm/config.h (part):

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// ---------------------------------------------------------------------------
#define PIN_E220_TXD   7    // Nano RX  <- E220 TXD
#define PIN_E220_RXD   8    // Nano TX  -> divider -> E220 RXD
#define PIN_E220_AUX   6    // Nano in  <- E220 AUX (high = idle)
#define PIN_E220_M0    9    // Nano out -> divider -> E220 M0
#define PIN_E220_M1    10   // Nano out -> divider -> E220 M1
#define PIN_LED        13
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// A4 = SDA, A5 = SCL: INA226 supply monitor (fixed by the Nano's I2C hardware)

// TOWER only
#define PIN_PA_SENSE   A0   // PA power-sense output (0-5 V) via divider
#define PIN_XV_SENSE   A1   // MKU 10 G5 CON1 pin 9 MON via divider
#define PIN_LO_LOCK    A2   // MKU 10 G5 CON1 pin 16 LD (3.3 V = locked), read as analog
#define PIN_PTT_SENSE  A3   // MKU CON1 pin 8 PTT out (active low, to the sequencer) via network
#define PIN_XV_RX      11   // Nano RX  <- level shifter <- MKU CON1 pin 11 TXD
#define PIN_XV_TX      12   // Nano TX  -> level shifter -> MKU CON1 pin 12 RXD

// ---------------------------------------------------------------------------
// Analog scaling (tower). The host converts mV to watts with your calibration
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#define LOCK_ACTIVE_HIGH  1
#define LOCK_THRESHOLD_MV 1650   // at the pin (no divider on A2)

// MKU 10 G5 CON1 pin 8: PTT out to the sequencer, active low. The tower only
// watches it, never drives it. Network (RK-302 Rev B, prototype rows 12-13):
//   line -> 100k to +5 V (so an open line reads high, ~2 V, not "keyed")
//   line -> 47k -> A3 -> 22k + 100 nF to GND   (safe up to ~15 V on the line)
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

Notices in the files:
README.md:
License:
MIT. © 2026 Rus Healy, K2UA.
License: MIT
